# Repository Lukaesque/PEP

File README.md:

## Set štampanih ploča namenjenih za učenje elektronike

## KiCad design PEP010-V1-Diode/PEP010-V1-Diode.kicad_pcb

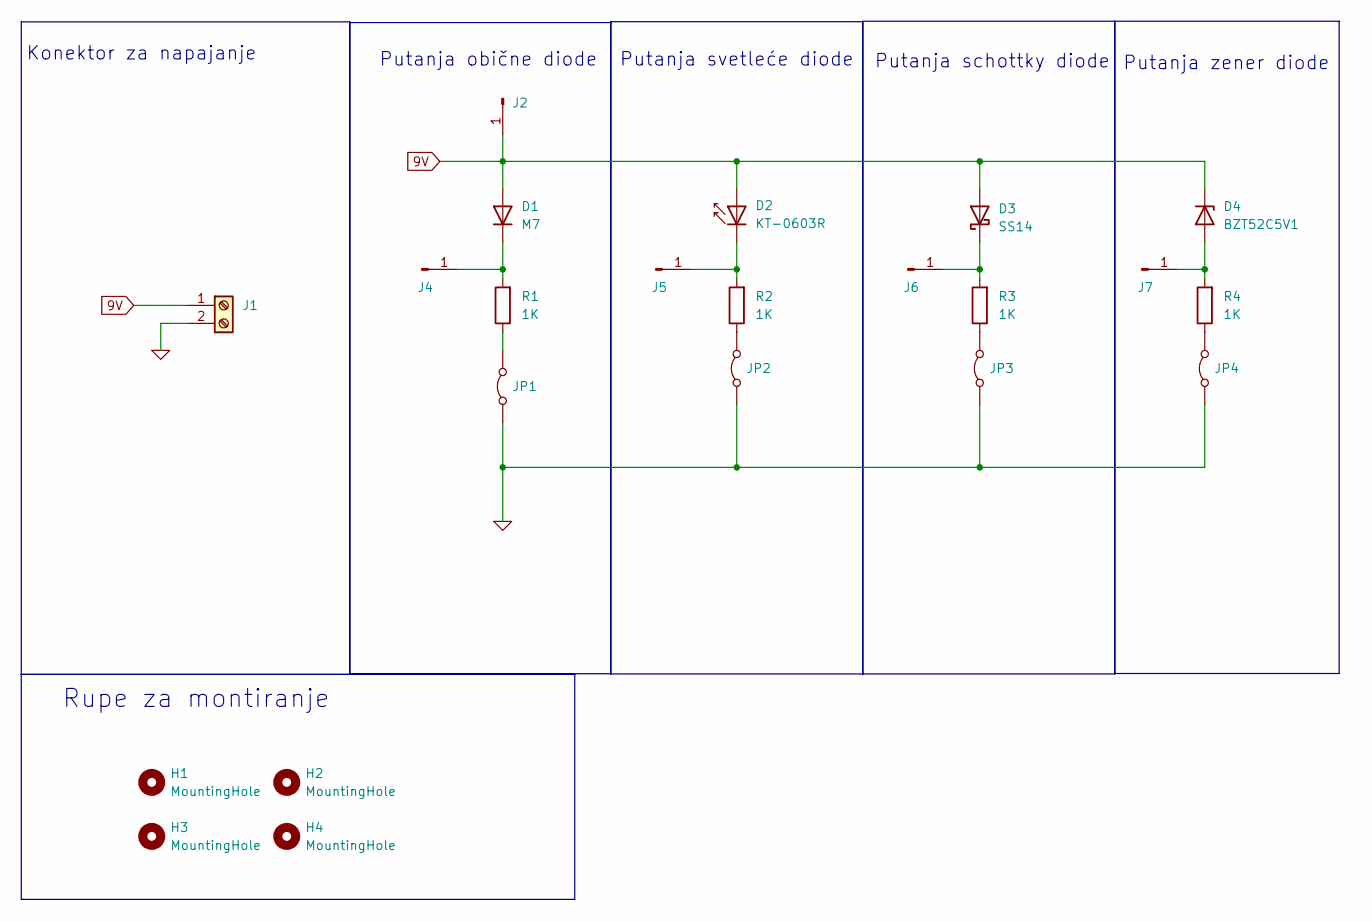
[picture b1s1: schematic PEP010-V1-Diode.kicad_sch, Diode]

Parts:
D1: M7; D_SMA; LCSC C95872
D2: KT-0603R; D_0603; LCSC C2286
D3: SS14; D_SMA; LCSC C2480
D4: BZT52C5V1; D_SOD-123; LCSC C173407
H1, H2, H3, H4: MountingHole; MountingHole_3.2mm_M3_ISO14580_Pad_TopBottom
J1: Screw_Terminal_01x02; TerminalBlock_Phoenix_MKDS-1,5-2-5.08_1x02_P5.08mm_Horizont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
J2, J4, J5, J6, J7: Conn_01x01_Pin; PinHeader_1x01_P2.54mm_Vertical
JP1, JP2, JP3, JP4: Jumper_2_Bridged; PinHeader_1x02_P2.54mm_Vertical
R1, R2, R3, R4: 1K; R_1206_3216Metric; LCSC C4410

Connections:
0: J1.2, JP1.1 (A), JP2.1 (A), JP3.1 (A), JP4.1 (A)
9V: D1.2 (A), D2.2 (A), D3.2 (A), D4.1 (K), J1.1, J2.1
unnamed: D1.1 (K), J4.1, R1.2
unnamed: D2.1 (K), J5.1, R2.2
unnamed: D3.1 (K), J6.1, R3.2
unnamed: D4.2 (A), J7.1, R4.2
unnamed: JP1.2 (B), R1.1
unnamed: JP2.2 (B), R2.1
unnamed: JP3.2 (B), R3.1
unnamed: JP4.2 (B), R4.1

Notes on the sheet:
Rupe za montiranje
Putanja svetleće diode
Konektor za napajanje
Putanja obične diode
Putanja schottky diode
Putanja zener diode

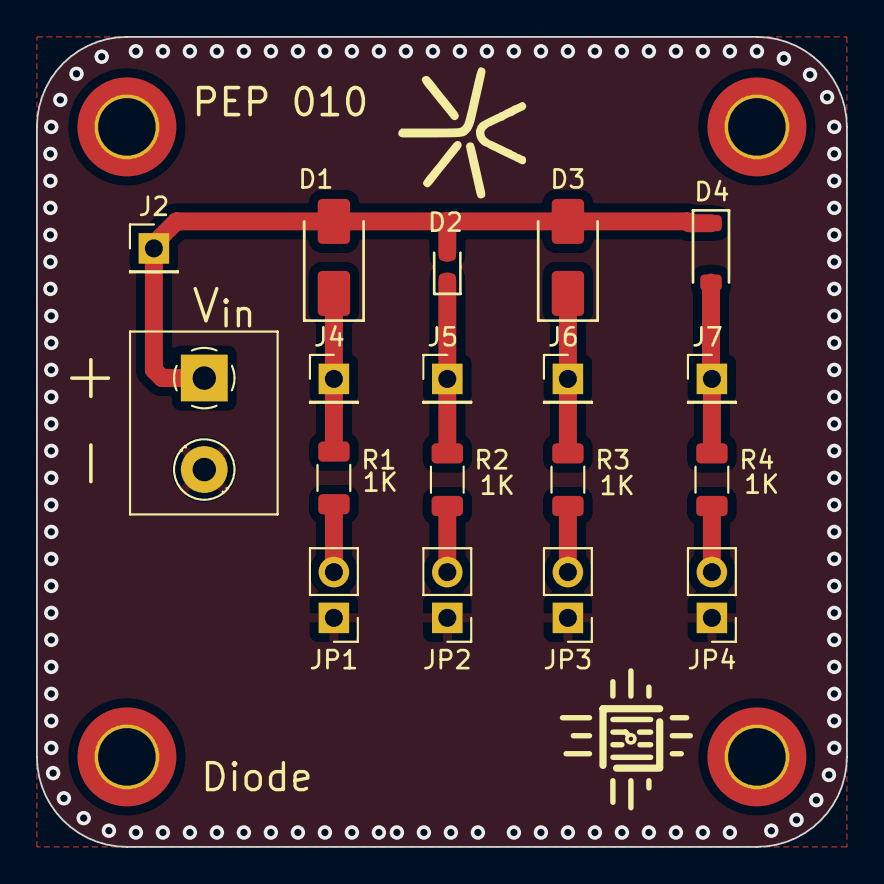
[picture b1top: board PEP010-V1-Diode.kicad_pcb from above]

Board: 2 copper layers, 45.0 x 45.0 mm, 22 parts (0 on the bottom side), 10 nets.

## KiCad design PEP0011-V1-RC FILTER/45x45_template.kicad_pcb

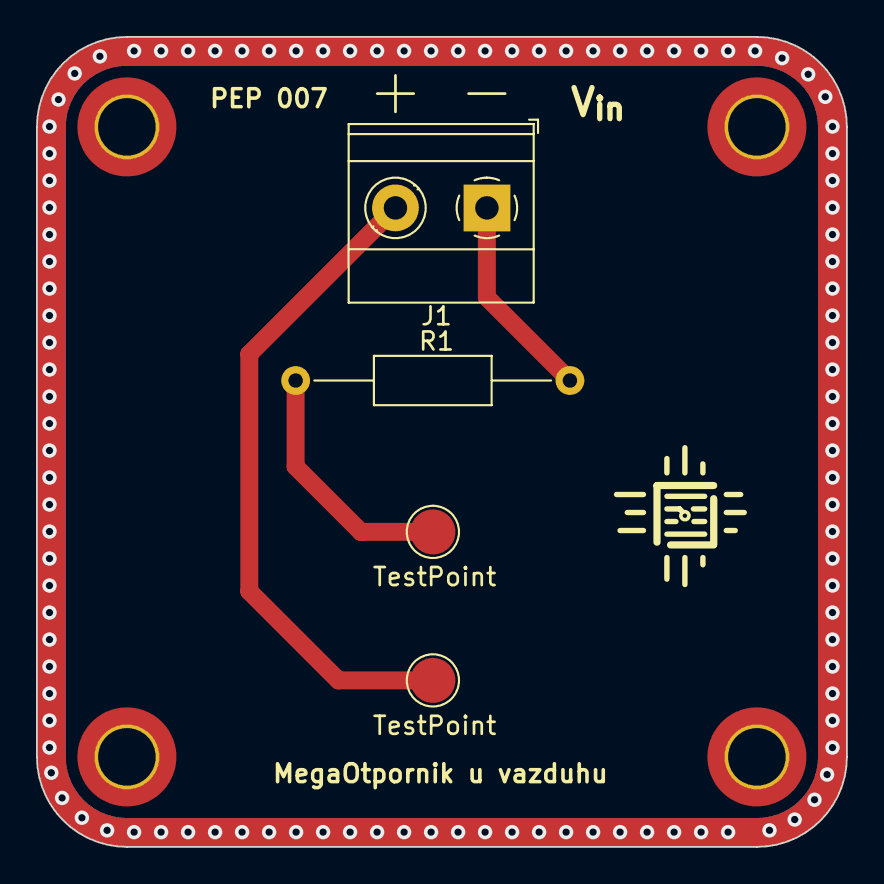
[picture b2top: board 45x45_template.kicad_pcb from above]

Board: 2 copper layers, 45.0 x 45.0 mm, 8 parts (0 on the bottom side), 3 nets.

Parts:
H1, H2, H3, H4: MountingHole; MountingHole_3.2mm_M3_ISO14580_Pad_TopBottom
J1: Screw_Terminal_01x02; TerminalBlock_Phoenix_MKDS-1,5-2-5.08_1x02_P5.08mm_Horizont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
R1: 1Meg; R_Axial_DIN0207_L6.3mm_D2.5mm_P15.24mm_Horizontal
TP2, TP2#2: TestPoint; TestPoint_Pad_D2.5mm

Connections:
0: J1.2, TP2#2.2 (1)
Input voltage: J1.1, R1.2
unnamed: R1.1, TP2.1

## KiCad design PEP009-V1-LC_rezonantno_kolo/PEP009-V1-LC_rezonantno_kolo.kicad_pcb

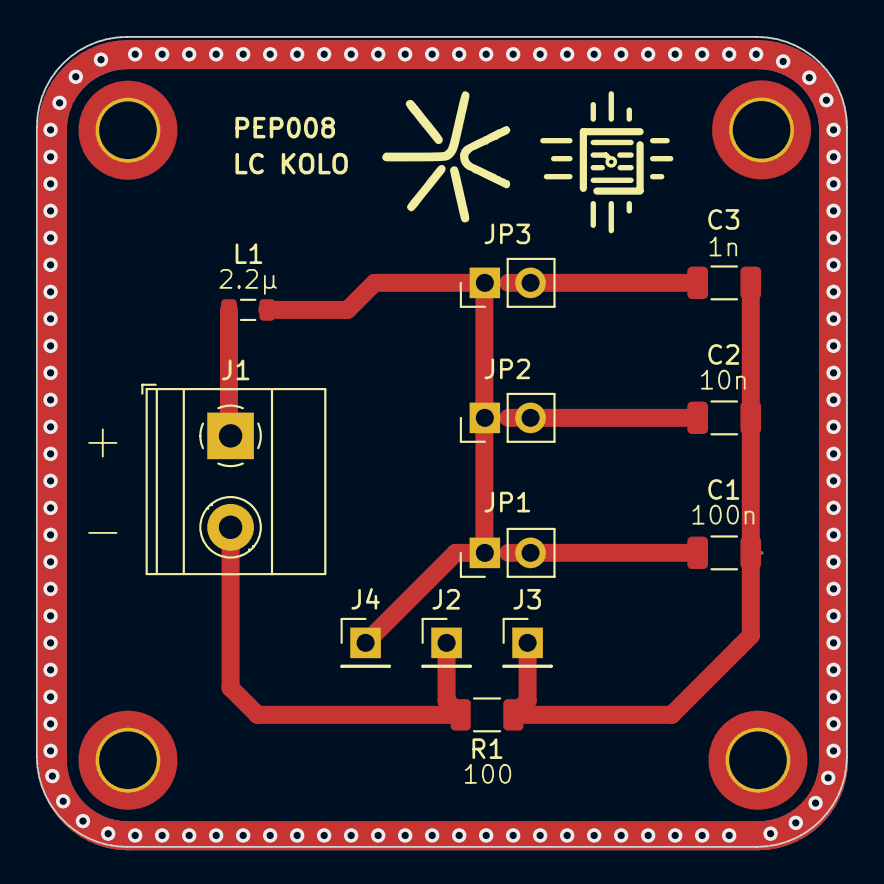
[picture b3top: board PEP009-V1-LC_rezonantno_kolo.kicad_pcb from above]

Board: 2 copper layers, 45.0 x 45.0 mm, 16 parts (0 on the bottom side), 7 nets.

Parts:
C1: 100n; C_1206_3216Metric
C2: 10n; C_1206_3216Metric
C3: 1n; C_1206_3216Metric
H1, H2, H3, H4: MountingHole; MountingHole_3.2mm_M3_ISO14580_Pad_TopBottom
J1: Screw_Terminal_01x02; TerminalBlock_Phoenix_MKDS-1,5-2-5.08_1x02_P5.08mm_Horizont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
J2, J3, J4: Conn_01x01_Pin; PinHeader_1x01_P2.54mm_Vertical
JP1, JP2, JP3: Jumper; PinHeader_1x02_P2.54mm_Vertical
L1: 2.2µ; L_0805_2012Metric
R1: 100; R_1206_3216Metric

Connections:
GND: J1.2, J2.1, R1.2
Input voltage: J1.1, L1.1
unnamed: C1.2, C2.2, C3.2, J3.1, R1.1
unnamed: J4.1, JP1.1 (A), JP2.1 (A), JP3.1 (A), L1.2
unnamed: C1.1, JP1.2 (B)
unnamed: C2.1, JP2.2 (B)
unnamed: C3.1, JP3.2 (B)

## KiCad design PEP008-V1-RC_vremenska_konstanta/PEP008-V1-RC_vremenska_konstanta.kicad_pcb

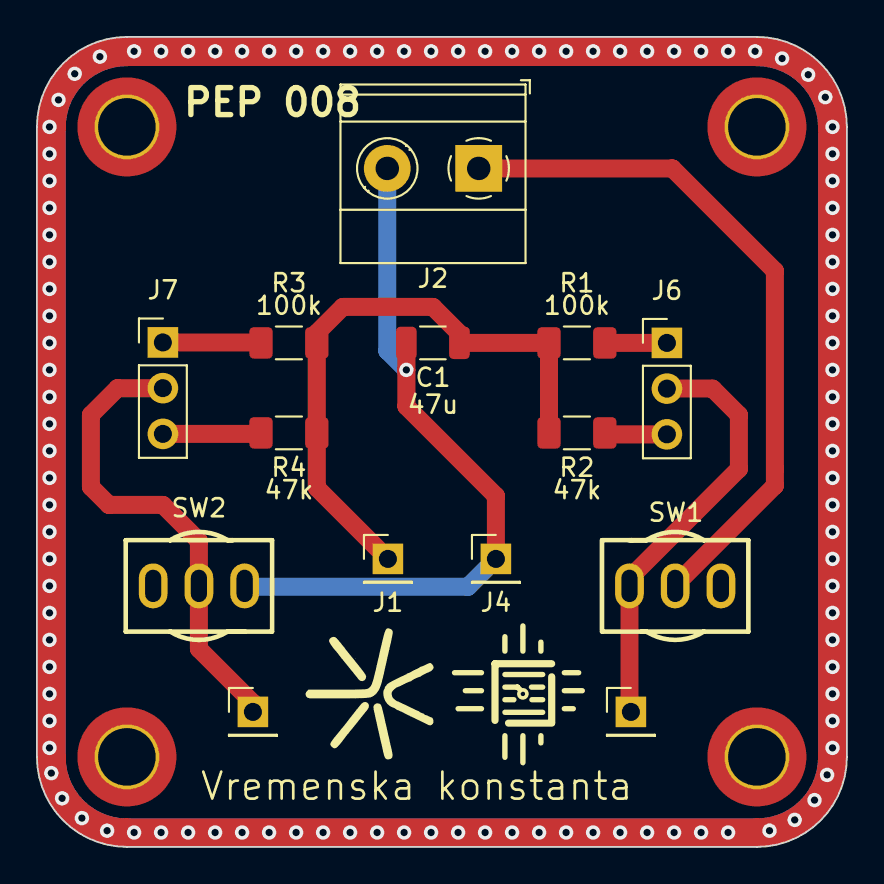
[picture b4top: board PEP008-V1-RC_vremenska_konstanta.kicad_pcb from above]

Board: 2 copper layers, 45.0 x 45.0 mm, 18 parts (0 on the bottom side), 9 nets.

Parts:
C1: 47u; C_1206_3216Metric
H1, H2, H3, H4: MountingHole; MountingHole_3.2mm_M3_ISO14580_Pad_TopBottom
J1, J3, J4, J5: Conn_01x01_Pin; PinHeader_1x01_P2.54mm_Vertical
J2: Screw_Terminal_01x02; TerminalBlock_Phoenix_MKDS-1,5-2-5.08_1x02_P5.08mm_Horizont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
J6, J7: Conn_01x03_Pin; PinHeader_1x03_P2.54mm_Vertical
R1, R3: 100k; R_1206_3216Metric_Pad1.30x1.75mm_HandSolder
R2, R4: 47k; R_1206_3216Metric_Pad1.30x1.75mm_HandSolder
SW1, SW2: SW_SPDT; SW-TH_2MS1T1B1M1QES-5

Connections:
0: C1.2, J2.2, J4.1, SW2.1 (A)
Input voltage: J2.1, SW1.2 (B)
unnamed: J3.1, J7.2, SW2.2 (B)
unnamed: J5.1, J6.2, SW1.1 (A)
unnamed: J6.1, R1.1
unnamed: J6.3, R2.1
unnamed: J7.1, R3.1
unnamed: J7.3, R4.1
Output voltage: C1.1, J1.1, R1.2, R2.2, R3.2, R4.2

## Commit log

2025-07-04 Added 90x90 template.
2025-07-20 mmm.
2025-07-20 Messagessssssssssss v
2025-07-20 I am tring smth now fr
2025-07-20 No real comment No real comment
2025-07-20 fixing my mistakes
2025-07-20 okay finally fixing them again
2025-07-21 Dodat silskcreen za potenciometar, prva verzija RC filtera ?
